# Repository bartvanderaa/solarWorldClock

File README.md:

solarWorldClock
===============

The Arduino based Solar World Clock<br>

Bart van der Aa<br>
info@bartvanderaa.com<br>
2013-2014<br>
 
General notes:<br>
The Solar World Clock (SWC) project has been in my mind for about 10 years now, and finally I found a suitable platform (the Arduino) to actually built it. 
But, first things first, what is the WSC project about? And secondly, how can we built one?<br>

The first question is actually fairly easy to answer. Imagine the map of the world where the sun's intensity is projected on the surface of this map. One could read the approximate time by tracing the location of the sun, just by identifying on which parts of the globe it is day- or nighttime. This, in brief, is the working principle of the WSC. Obviously, it is difficult to know the time in absolute terms, but who needs that anyway ;-) <br>
 
Notes on algorithm:<br>
The program uses a real-time-clock (RTC) to keep track of date and time. Based on date, time, and location the solar intensity is computed. A vector of intensity values (0-255) is then send to ShiftPWM to control an array of LEDs. Time can now be read based on the digitally projected solar intensity. <br>
 
Sunset-Sunrise part:<br>
Eastern longitude positive, Western longitude negative, Northern latitude positive and Southern latitude negative. <br>
 
PWM part:<br>
If flickering of the LEDs occurs try to adjust the PWM frequency.<br>
 
Credits go to:<br>
Solar intensity part by The Renewable Resource Data Center (RReDC), downloaded 2014;<br>
RTC part by Michael Margolis, downloaded 2014<br>
PWM part by Elco Jacobs, updated August 2012<br>

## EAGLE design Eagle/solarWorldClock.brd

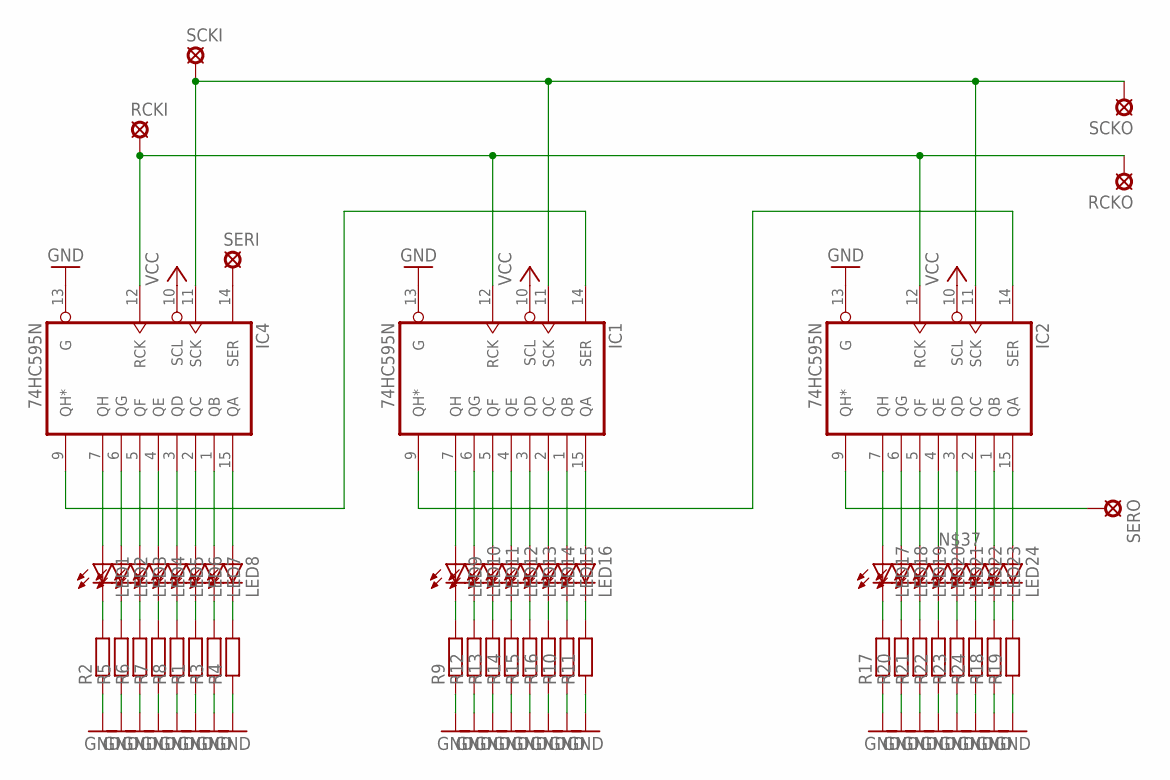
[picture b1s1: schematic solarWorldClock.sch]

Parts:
IC1, IC2, IC4: 74HC595N; DIL16
LED1, LED2, LED3, LED4, LED5, LED6, LED7, LED8, LED9, LED10, LED11, LED12, LED13, LED14, LED15, LED16, LED17, LED18, LED19, LED20, LED21, LED22, LED23, LED24: LEDLZR181; LZR181
R1, R2, R3, R4, R5, R6, R7, R8, R9, R10, R11, R12, R13, R14, R15, R16, R17, R18, R19, R20, R21, R22, R23, R24: R-EU_0207/7; 0207/7
RCKI: LSP10
RCKO: LSP10
SCKI: LSP10
SCKO: LSP10
SERI: LSP10
SERO: LSP10

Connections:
GND: IC1.8 (GND), IC1.13 (G), IC2.8 (GND), IC2.13 (G), IC4.8 (GND), IC4.13 (G), R1.1, R2.1, R3.1, R4.1, R5.1, R6.1, R7.1, R8.1, R9.1, R10.1, R11.1, R12.1, R13.1, R14.1, R15.1, R16.1, R17.1, R18.1, R19.1, R20.1, R21.1, R22.1, R23.1, R24.1
unnamed: IC4.7 (QH), LED1.A
unnamed: LED1.K (C), R2.2
unnamed: IC4.6 (QG), LED2.A
unnamed: IC4.5 (QF), LED3.A
unnamed: IC4.4 (QE), LED4.A
unnamed: IC4.3 (QD), LED5.A
unnamed: IC4.2 (QC), LED6.A
unnamed: IC4.1 (QB), LED7.A
unnamed: IC4.15 (QA), LED8.A
unnamed: LED2.K (C), R5.2
unnamed: LED3.K (C), R6.2
unnamed: LED4.K (C), R7.2
unnamed: LED5.K (C), R8.2
unnamed: LED6.K (C), R1.2
unnamed: LED7.K (C), R3.2
unnamed: LED8.K (C), R4.2
unnamed: IC1.7 (QH), LED9.A
unnamed: IC1.6 (QG), LED10.A
unnamed: IC1.5 (QF), LED11.A
unnamed: IC1.4 (QE), LED12.A
unnamed: IC1.3 (QD), LED13.A
unnamed: IC1.2 (QC), LED14.A
unnamed: IC1.1 (QB), LED15.A
unnamed: IC1.15 (QA), LED16.A
unnamed: LED9.K (C), R9.2
unnamed: LED10.K (C), R12.2
unnamed: LED11.K (C), R13.2
unnamed: LED12.K (C), R14.2
unnamed: LED13.K (C), R15.2
unnamed: LED14.K (C), R16.2
unnamed: LED15.K (C), R10.2
unnamed: LED16.K (C), R11.2
unnamed: IC2.9 (QH*), SERO.MP
unnamed: IC1.14 (SER), IC4.9 (QH*)
unnamed: IC2.7 (QH), LED17.A
unnamed: IC2.6 (QG), LED18.A
unnamed: IC2.5 (QF), LED19.A
unnamed: IC2.4 (QE), LED20.A
unnamed: IC2.3 (QD), LED21.A
unnamed: IC2.2 (QC), LED22.A
unnamed: IC2.1 (QB), LED23.A
unnamed: IC2.15 (QA), LED24.A
unnamed: LED17.K (C), R17.2
unnamed: LED18.K (C), R20.2
unnamed: LED19.K (C), R21.2
unnamed: LED20.K (C), R22.2
unnamed: LED21.K (C), R23.2
unnamed: LED22.K (C), R24.2
unnamed: LED23.K (C), R18.2
unnamed: LED24.K (C), R19.2
unnamed: IC1.9 (QH*), IC2.14 (SER)
unnamed: IC1.12 (RCK), IC2.12 (RCK), IC4.12 (RCK), RCKI.MP, RCKO.MP
unnamed: IC1.11 (SCK), IC2.11 (SCK), IC4.11 (SCK), SCKI.MP, SCKO.MP
unnamed: IC4.14 (SER), SERI.MP
VCC: IC1.10 (SCL), IC1.16 (VCC), IC2.10 (SCL), IC2.16 (VCC), IC4.10 (SCL), IC4.16 (VCC)

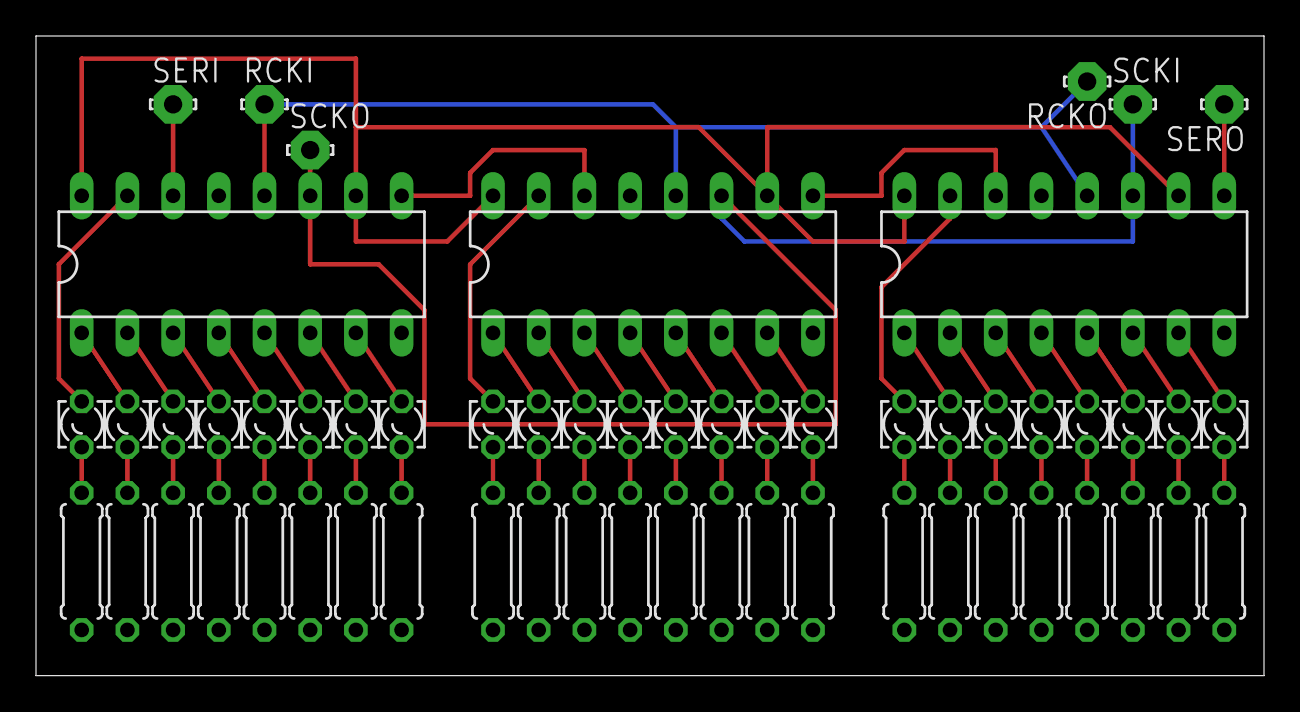
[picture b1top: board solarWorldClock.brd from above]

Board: 2 copper layers, 68.2 x 35.5 mm, 57 parts (0 on the bottom side), 56 nets.

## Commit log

2014-08-30 Initial version
    Initial version for github
2014-08-30 Update README
    Update readme text
2014-08-30 update README
    update readme
2014-09-21 Eagle files added
    Eagle files for SWC added to the repository
